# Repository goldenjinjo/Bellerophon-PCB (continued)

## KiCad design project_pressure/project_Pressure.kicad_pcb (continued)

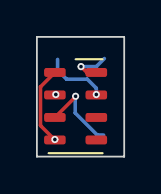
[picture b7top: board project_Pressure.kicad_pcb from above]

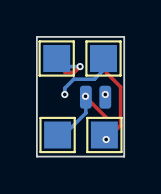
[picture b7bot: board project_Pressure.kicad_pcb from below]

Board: 2 copper layers, 4.8 x 6.7 mm, 6 parts (5 on the bottom side), 5 nets.

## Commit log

2022-02-04 Create temp
2022-02-04 Add files via upload
    Completed footprints and symbols for all sensors in first iteration, first revision of schematic
2022-02-24 added dimensionally accurate borders
2022-02-25 added borders
2022-02-25 Added more components and attached footprints
    added voltage regulator for rfd900, battery connectors and updated footprints for all components.
2022-02-25 updated cache and added backup files
2022-02-25 outlined approximate geometry of pcb and made some connections
2022-02-26 changed connector footprints from horizontal to vertical
2022-02-26 adding sma coaxial connectors, footprint may change
2022-02-27 matched RFD900 footprint borders with datasheet
2022-03-04 added voltage regulator to schematic and pcb
2022-03-22 removed one of connectors, fixed connector schematic wiring
2022-03-22 created sma-connector schematic and footprint and implemented 3D step file
2022-03-23 fixed UART wiring for gps and modem
2022-03-23 finalized board dimensions (50x120mm) and component positioning. completed draft of traces
2022-03-30 removed a wire
2022-03-31 added vias to trace power
2022-03-31 added ground plane and vias. completed trace routing
2022-03-31 adjusted trace width for 5V power, added mounting holes, some 3D models
2022-03-31 added logo and cleaned up some silkscreens on PCB
2022-03-31 extended ground plane to edge of board, created 3mm fillet for ground plane
2022-03-31 added no connection flag to schematics, fixed minor mistakes on PCB and in footprints
2022-03-31 fixed BNO055 pin numbering, cleaned up schematic
2022-04-06 decreased via sizes
2022-04-06 set to ignore schematic backup file
2022-04-06 modified some trace lengths
2022-04-06 removed adafruit sensors from RFD900 library
2022-04-06 mistaken edit
2022-04-06 created bellerophon project directory and imported symbols
2022-04-06 added voltage regulator circuitry
2022-04-06 added chute deployment mosfets
    added chute deployment mosfets
2022-04-07 Revert "added MPL3115A2 to Bellephrone Schematic"
2022-04-07 connected PY1 and PY2 pins to teensy
2022-04-07 created schematic and footprint for Adafruit SD Breakout Board
2022-04-07 improved dimensional accuracy of Adafruit BNO055
2022-04-07 LED/Buzzer circuits added to bellerophon schematic
2022-04-08 PaulBess: added drawing for Adafruit MPL3115A2, goldenjinjo: changed chute deployment resistors to 5 ohms
2022-04-08 fixed misalignment on SD chip symbol; added SD chip drawing to schematic
2022-04-08 improved dimensional accuracy of MPL3115A2 footprint
2022-04-09 Add Adafruit ICM20948symbol to adafruit library
2022-04-09 add ICM20948 footprint template, to be completed
2022-04-10 Add Adafruit ICM20948 footprint to adafruit library. Also add Adafruit ICM20948 wiring to the schematics file
2022-04-10 fix fab name text on footprint, change ICM wiring to SDA0, SCL0 pins
2022-04-14 Update bellerophon.kicad_sch
    updated screw terminal. footprints are ok for the mosfets T-220 form. 5W Resistor through hole assumed a distance of 10mm or so between holes (looks like a big resistor 25mm long about 7mm wide. Unkn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
2022-04-15 LED and Buzzer footprints added
2022-04-18 Update the schematic of the voltage regulator. Add the footprint of the switching diode.
2022-04-18 add footprints for resistors and diode
2022-04-18 add voltage regulator and teensy footprint libraries and assign footprints to symbols in schematic
2022-04-18 add terminal block footprints to schematic and update pcbnew
2022-04-18 add bulky resistor footprints
2022-04-20 change teensy footprint to THT, change some resistors, layed out components and boardcut in pcbnew
2022-04-20 change some teensy pins, reorganise component placement
2022-04-21 change capacitor footprint to D10mm
2022-04-22 add second buzzer
2022-04-22 add mounting holes, refined component placement
2022-04-22 curved board edges and reduced height to 98 mm
2022-04-22 refine silkscreen component description
2022-04-22 change capacitor to rectangle footprint, add remaining silkscreens
2022-04-22 add silkscreen to missing sides of ICM20948, SPI-Flash, and MPL3115A2
2022-04-22 Update pinhole size in the diode footprint and update diode footprint in schematic
2022-04-22 update diode footprint on pcbnew
2022-04-22 add no-connection flags to un-used teensy pins
2022-04-22 add signal traces to PCB
2022-04-22 fix numbering error on diode footprint
2022-04-22 add power traces and filled ground area
2022-04-22 add back silkscreen
2022-04-22 small modifications to silkscreen
2022-04-23 small modifications to PCB wiring and silkscreen positioning
2022-04-23 move teensy 4.0 silkscreen off of copper wire
2022-04-26 rewire pyro to source directly from battery, remove via, clean up tracks
2022-04-29 change battery traces from parrallel to series, increase spacing of some traces from through hole pins
2022-04-29 fix led symbol so GND is pin 2 and not pin 4
2022-04-29 add diode footprint and stp file, remove old gbr files
2022-04-29 increase diode pin size to 1.5mm, add 3D model of diode
2022-04-29 increase SPI flash footprint pin size to 1mm so it fits with standardized connectors
2022-04-29 add jlc tag for production, add gerber file
2022-05-04 add datasheets
2022-05-04 add breakout boards
2022-05-04 Update bellerophon.kicad_sch
    Added surface mount resistors (1206 form) and surface mount Mosfet see links attached to the components for the ones to buy off RS components.
    Added a continuity check, this circuit is always live but draws a tiny current, it can be used to check the eMatch is present. A high signal of ~2.4-3V (via a voltage divider) depending on power sour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
    Brown out capacitor wont be useful here I don'
2022-05-04 Surface Mounts + Continuity
    Added surface mount resistors (1206 form) and surface mount Mosfet see links attached to the components for the ones to buy off RS components.
    Added a continuity check, this circuit is always live but draws a tiny current, it can be used to check the eMatch is present. A high signal of ~2.4-3V (via a voltage divider) depending on power sour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
    Brown out capacitor wont be useful here I don't
2022-05-04 Update bellerophon.kicad_sch
    updated mosfet label to PSMN4R3-30BL
2022-05-09 remove adafruit mpl3115a2 and replace with SMT circuit
2022-05-09 replace remaining resistors and capacitors with SMT components
2022-05-12 fix overlapping vias, move pyro resistor silkscreen
2022-05-12 add missing breakout board files
2022-05-12 add SPI flash breakout via upload
2022-05-12 fix nested repo issue with breakout boards
2022-05-12 remove breakout board
2022-05-12 return breakout board, fix error
2022-05-12 replace THT voltage regulator with SMT, 750mA SOT-89-3
2022-05-12 remove second battery input, combine battery and switch terminals into a single 1x4 terminal
2022-05-12 replace switching diode with SMT PFET
2022-05-12 correct name on voltage regulator
2022-05-12 add datasheets, change regulator to a ht7350-a
2022-05-12 add f.fab and f.crtyrd to teensy 4 footprint, remove interior pins
2022-05-17 SD breakout convert to surface mount
2022-05-20 Modify schematic for SMT Flash chip
2022-05-23 create footprint for xtsd and add to pcb
2022-05-23 remove second buzzer
2022-05-24 Replace ICM breakout board schematic with SMT BNO055 circuit
2022-05-25 connect BNO055 pins to SCL0 and SDA0
2022-05-25 add bno055 circuit to pcb, design new draft layout for SMT
2022-05-26 change sensor resistor to 0805
2022-05-26 change mount holes to m3, resize board
2022-05-26 remove silkscreen reference designators
2022-05-26 move nand chip to right side of teensy
2022-05-26 add project_pressure kicad project
2022-05-26 remove extra folder
2022-05-27 add step file and remove old version of board
2022-06-02 change pin assignments to better fit layout
2022-06-02 change pyro mosfet to smaller SOT-23, shrink board to 85 mm
2022-06-02 change buzzer pin to 14, rearange power circuitry
2022-06-02 change BNO055 crystal to 3215 SMD
2022-06-02 remove interupt, reboot and I2Caddress connection from BNO055
2022-06-02 finalized bno055 circuitry and placement
2022-06-02 add back i2cADDR pin for bno055
2022-06-02 finalize MPL circuitry
2022-06-02 reduce length to 79mm
2022-06-07 add some IMU traces
2022-06-07 complete IMU traces
2022-06-08 route all signal traces
2022-06-08 add ground plane on top and bottom, 3.3V plane on inCu2
2022-06-08 increase via diameter to 0.5mm for all vias
2022-06-08 add via for gnd and power planes
2022-06-08 increase spacing of LED pin
2022-06-08 align mounting holes
2022-06-08 add logo and silkscreen
2022-06-09 reduce power plane area
2022-06-09 increase BNO055 components and vias spacing
2022-06-09 modify silkscreen
2022-06-15 reduce pcb thickness to 1.6mm, reduce power plane size
2022-06-19 add 3 fiducials, move components to accomodate
2022-06-19 extend board length to 37mm to comply with mounting regulations
2022-06-19 actually increase width to 37mm
2022-06-19 add JLC component numbers to all parts, define drill origin
2022-06-23 add missing connection of VDD to power (oops) and set reset pin to high
2022-06-25 simplify silkscreen of switch terminal, remove old step file. This is the version for production file V2.
2022-06-25 Update README.md
    updated parts for bellerophon
2022-06-28 export Pegasus project file to new repo
2022-06-28 export project-pressure project file to new repo
2022-06-28 Update README.md
    remove pegasus parts list
2022-07-13 rename pyro and led pins to more useful names, change global labels in schematic to local
2022-07-13 replace pyro mosfets with correct symbol to fix the incorrect numbering of gate, source and drain.
2022-07-13 restore archive of v1 of bellerophon
2022-08-09 add gps datasheet
2022-08-10 add silkscreen to indicate v2.1
2022-09-25 add dimensions
2022-09-28 no update
2022-10-07 change screw terminal reference designators to J1, J2
2023-02-06 add two more pyro channels, reduce screw terminal size, change buzzer, replace IMU with breakout board
2023-02-06 add smaller buzzer
2023-02-06 add screw terminal footprints, tidy up pyro circuit placement
2023-02-09 add smaller GPIO connectors, add symbol for highG accelerometer, complete schematic design for 2/3 accelerometers
2023-02-10 small modifications to placement
2023-02-10 first draft of component placement
2023-02-11 increase height, add anti brownout capacitor, add pinouts for pyros
2023-02-12 first draft of traces
2023-02-16 replace RGB LED with 3 LEDs
2023-02-17 add lcsc tags to all additional components
2023-02-17 make all SMD footprints on front layer, move screw terminals to bottom layer
2023-02-17 smallimprovements to schematic
2023-02-17 fix uup edge cut, create gerbers
2023-02-17 fix some lcsc part numbers and footprints
2023-02-17 add 3d models to THT components
2023-02-17 forgot to save
2023-02-17 improve models, add step file
2023-02-18 create temporary solution to display 4 pin screw terminal models, add mounting hole spacing dimensions
2023-04-26 fix I2C0 wiring to wrong place on microcontroller
2023-04-26 remove pyro test circuit, as it created a permanent gnd
2023-04-26 remove pyro led as it never recieved power
2023-04-27 remove high G accelerometer, as was not used
2023-04-27 replace power and pyro connectors with 5mm spacing
2023-04-27 reposition pyro circuit to fit new components
2023-04-27 add reverse polarity protection
2023-06-04 clean up component placing, route new traces, add TVS diode for surge protection, combine sensor I2C into same pins
2025-01-22 remove step files
2025-04-23 add images, update files to kicad 8
2025-04-23 clean up schematic artefacts, add section that clearly shows pinouts
2025-04-23 remove deprecated datasheets and breakout boards
2025-04-23 remove step files, manufacturing files, temp files, update gitignore for more temp files
2025-04-23 remove temp file
2025-04-23 move logo files to inside component_libraries
